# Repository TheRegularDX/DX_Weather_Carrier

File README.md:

# DX_Weather_Carrier
custom board for my DX32 weather station project + PlatformIO code

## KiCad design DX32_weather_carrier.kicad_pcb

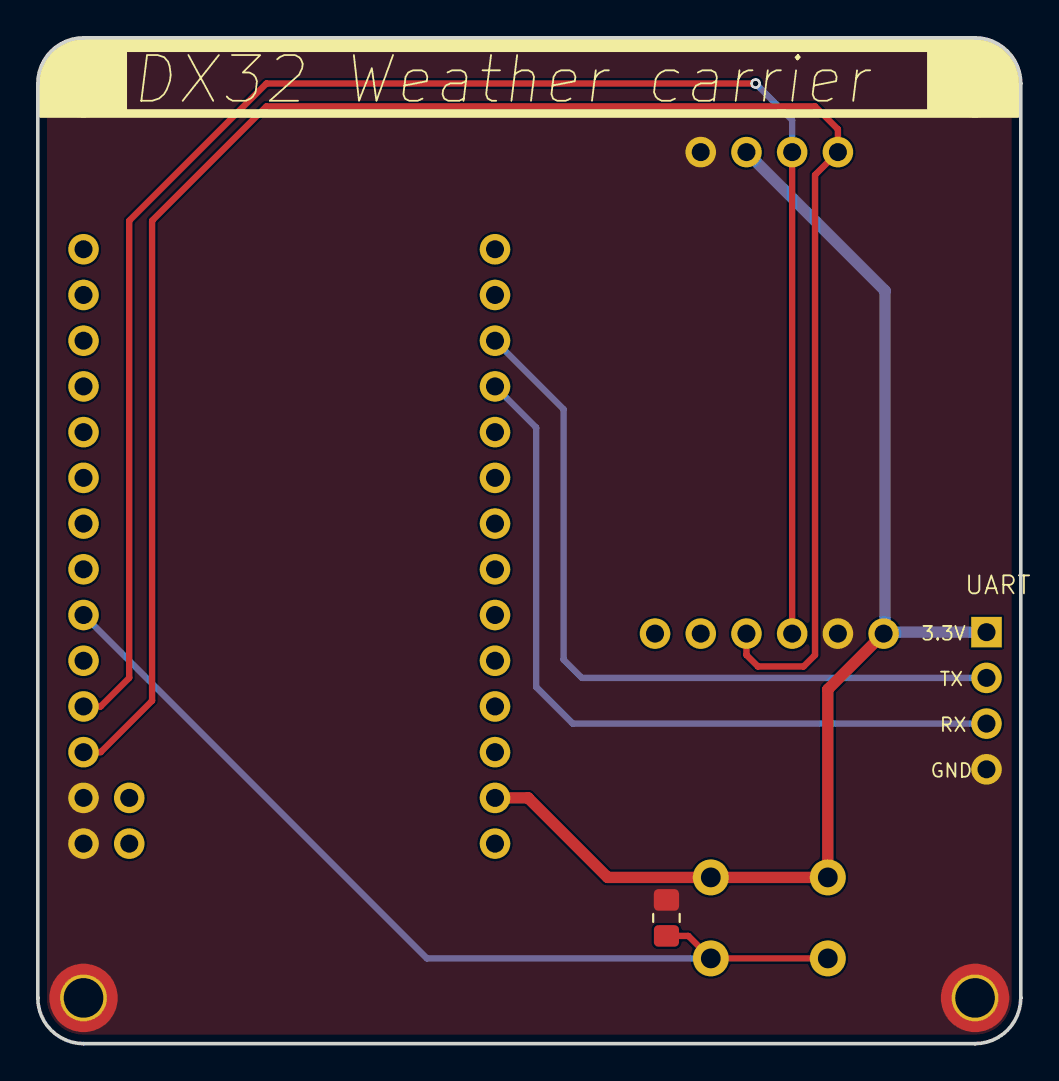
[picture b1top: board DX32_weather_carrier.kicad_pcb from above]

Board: 2 copper layers, 54.6 x 55.9 mm, 10 parts (0 on the bottom side), 7 nets.

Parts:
Button: User button; SW_PUSH_6mm
J1: UART; PinHeader_1x04_P2.54mm_Vertical
MountingHole1, MountingHole2, MountingHole3, MountingHole4: MountingHole_2.2mm_M2_DIN965_Pad_TopBottom
R1: R; R_0805_2012Metric_Pad1.20x1.40mm_HandSolder
U1: DX32A
U2: BME280
U3: SSD1306_OLED

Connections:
/RX: J1.3, U1.11 (RX)
/SCL: U1.25 (GPIO9_(SCL)), U2.4 (SCL), U3.3 (SCL)
/SDA: U1.26 (GPIO10_(SDA)), U2.3 (SDA), U3.4 (SDA)
/TX: J1.2, U1.12 (TX)
GND: J1.4, MountingHole1.1, MountingHole2.1, MountingHole3.1, MountingHole4.1, R1.2, U1.27 (GND), U1.28 (GND), U2.5 (GND), U3.1 (GND)
unnamed: Button.2, R1.1, U1.23 (GPIO8)
VCC: Button.1, J1.1, U1.2 (3.3V_(VCC)), U2.6 (VCC), U3.2 (VCC)

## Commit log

2024-04-03 Create LICENSE
